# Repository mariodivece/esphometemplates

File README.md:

# My ESPHome Templates

(Work in progress)

device classes:
 - [Analog Device Classes](https://www.home-assistant.io/integrations/sensor/#device-class)
 - [Binary Device Classes](https://www.home-assistant.io/integrations/binary_sensor/#device-class)
 - [NodeMCU 32s Pinout](https://www.waveshare.com/nodemcu-32s.htm)

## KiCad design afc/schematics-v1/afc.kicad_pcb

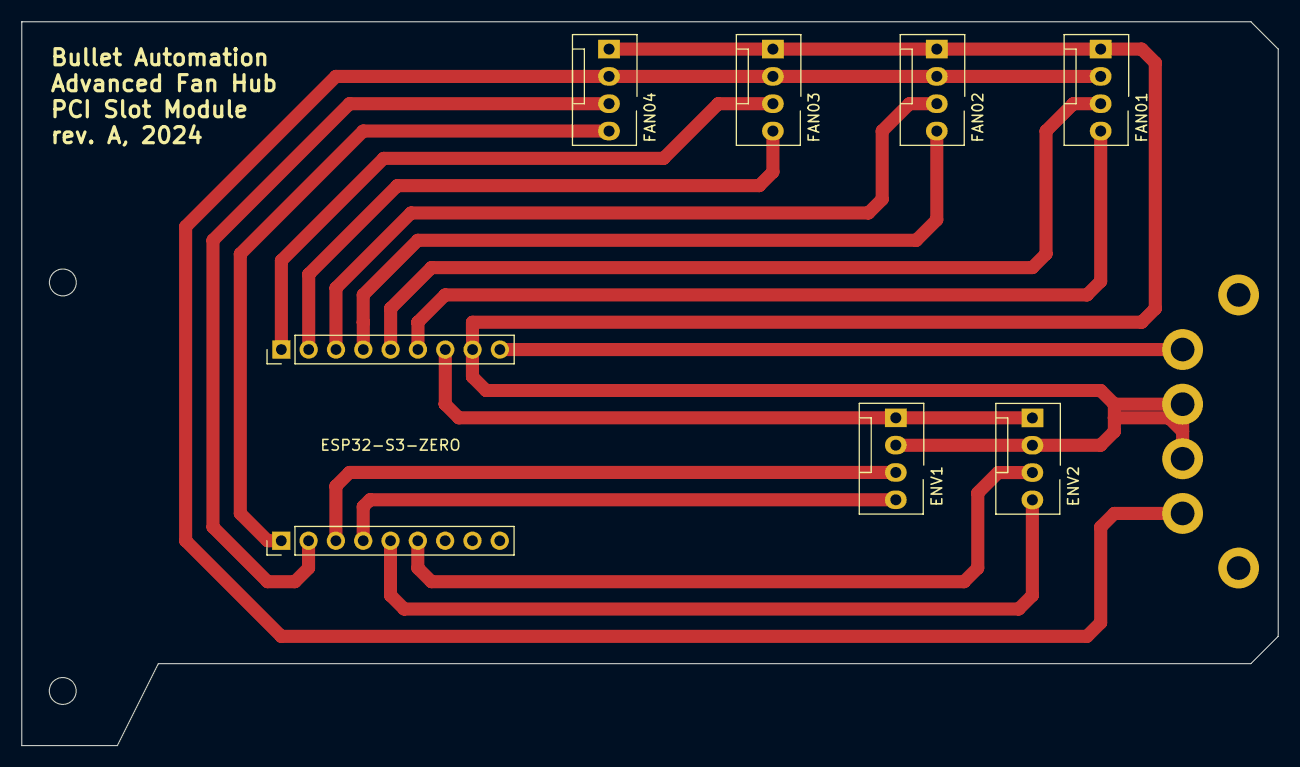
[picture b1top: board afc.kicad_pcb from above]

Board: 2 copper layers, 116.8 x 67.3 mm, 11 parts (0 on the bottom side), 15 nets.

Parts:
ATX2, ATX3: MountingHole_2.2mm_M2_DIN965_Pad
ENV1, ENV2: FAN_H4; FanPinHeader_1x04_P2.54mm_Vertical
ESP32_A: HA; PinHeader_1x09_P2.54mm_Vertical
ESP32_B: HB; PinHeader_1x09_P2.54mm_Vertical
FAN01: FAN_H1; FanPinHeader_1x04_P2.54mm_Vertical
FAN02: FAN_H2; FanPinHeader_1x04_P2.54mm_Vertical
FAN03: FAN_H3; FanPinHeader_1x04_P2.54mm_Vertical
FAN04: FAN_H4; FanPinHeader_1x04_P2.54mm_Vertical
PCIe_MNT_TOP: MountingHole_2.5mm

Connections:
3V3: ENV1.1, ENV2.1, ESP32_A.3V3
12V: FAN01.2, FAN02.2, FAN03.2, FAN04.2
GND: ATX2.2, ATX3.3, ENV1.2, ENV2.2, ESP32_A.GND, FAN01.1, FAN02.1, FAN03.1, FAN04.1
PWM1: ESP32_A.1, FAN01.4
PWM2: ESP32_A.3, FAN02.4
PWM3: ESP32_A.5, FAN03.4
PWM4: ESP32_B.7, FAN04.4
SCL_1: ENV1.3, ESP32_B.9
SCL_2: ENV2.3, ESP32_B.12
SDA_1: ENV1.4, ESP32_B.10
SDA_2: ENV2.4, ESP32_B.11
TACHO1: ESP32_A.2, FAN01.3
TACHO2: ESP32_A.4, FAN02.3
TACHO3: ESP32_A.6, FAN03.3
TACHO4: ESP32_B.8, FAN04.3

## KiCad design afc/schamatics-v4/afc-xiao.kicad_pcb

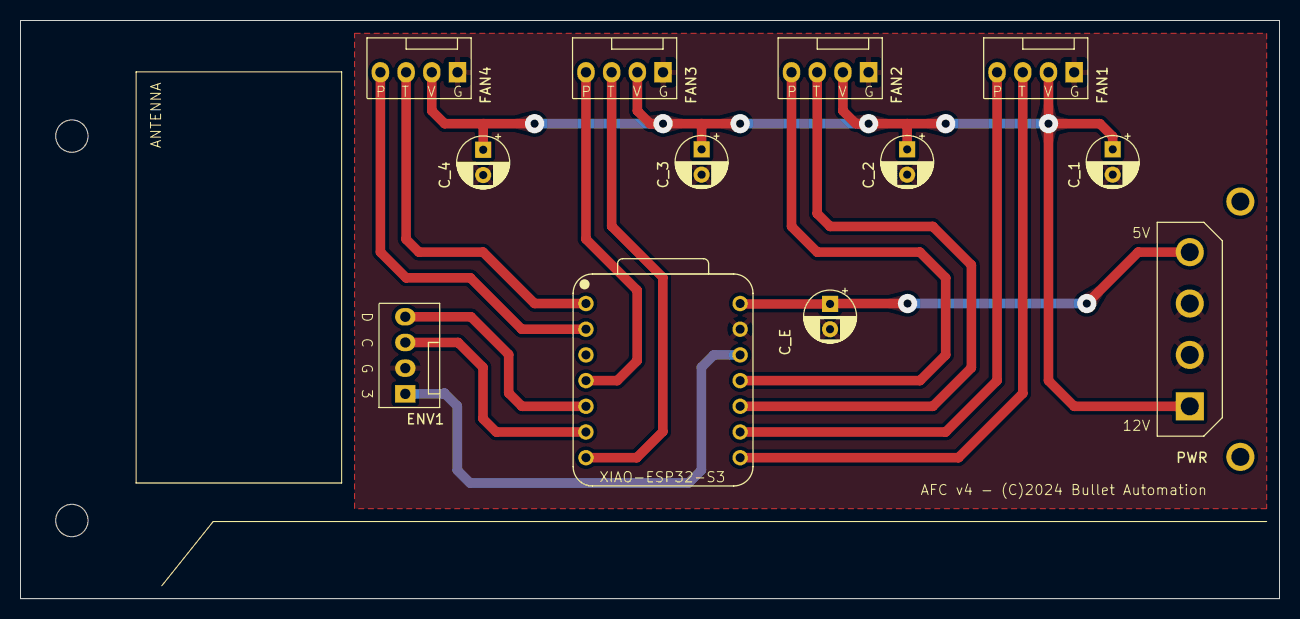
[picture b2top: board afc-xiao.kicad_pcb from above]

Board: 2 copper layers, 124.5 x 57.1 mm, 12 parts (0 on the bottom side), 14 nets.

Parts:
C_1, C_2, C_3, C_4: CP_Radial_D5.0mm_P2.50mm
C_E: CP_Radial_D5.0mm_P2.50mm
ENV1: PWM 4-pin Fan Header
FAN1, FAN2, FAN3, FAN4: PWM 4-pin Fan Header
PWR: Molex 4-Pin Power Connector
XIAO-ESP32-S3: XIAO-ESP32-S3-DIP; XIAO-ESP32S3-DIP

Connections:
3V3: ENV1.1, XIAO-ESP32-S3.12
5V: C_E.1, PWR.4, XIAO-ESP32-S3.14
12V: C_1.1, C_2.1, C_3.1, C_4.1, FAN1.2, FAN2.2, FAN3.2, FAN4.2, PWR.1
GND: C_1.2, C_2.2, C_3.2, C_4.2, C_E.2, ENV1.2, FAN1.1, FAN2.1, FAN3.1, FAN4.1, PWR.2, PWR.3, XIAO-ESP32-S3.13
PWM1: FAN1.4, XIAO-ESP32-S3.9
PWM2: FAN2.4, XIAO-ESP32-S3.11
PWM3: FAN3.4, XIAO-ESP32-S3.4
PWM4: FAN4.4, XIAO-ESP32-S3.2
SCL: ENV1.3, XIAO-ESP32-S3.6
SDA: ENV1.4, XIAO-ESP32-S3.5
TACHO1: FAN1.3, XIAO-ESP32-S3.8
TACHO2: FAN2.3, XIAO-ESP32-S3.10
TACHO3: FAN3.3, XIAO-ESP32-S3.7
TACHO4: FAN4.3, XIAO-ESP32-S3.1

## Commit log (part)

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2024-02-10 repo update
2024-02-10 removing subs
2024-02-10 remove subs
2024-02-10 fix typo
2024-02-10 updating 2g
2024-02-10 fixing hostname
2024-02-10 better name
2024-02-10 updating import definitions
2024-02-10 minor fix
2024-02-10 lab update
2024-02-10 simplifying substitutions
2024-02-10 minor doc
2024-02-10 simplifying 1g and 2g
2024-02-10 moving samples to folder
2024-02-10 adding d1 dimmer
2024-02-10 substitutions
2024-02-10 separating internaltemp
2024-02-10 trying out number configs
2024-02-10 scrubbing
2024-02-10 updating README
2024-02-12 Update sonoff-d1.yaml
    attempting to make the min and max levels UI-configurable
2024-02-12 upgrading sonoff d1
2024-02-12 fixing script
2024-02-12 testing
2024-02-13 attempting state synchronization
2024-02-13 minor fixup
2024-02-13 removing state accessor
2024-02-13 controller hanging
2024-02-13 toggle to sync
2024-02-13 minor id fix
2024-02-13 removing togglers
2024-02-13 removing unusable options
2024-02-13 gamma correct
2024-02-13 momentary support
2024-02-13 upgrading and adjusting modes
2024-02-14 adding initial version of shelly dimmer 2
2024-02-14 using correct name of dimmer device
2024-02-14 minor doc fix
2024-02-14 simplifying shelly dimmer2 firmware template
2024-02-14 splitting up shelly dimmer
2024-02-15 renaming and pointing to new package locations
2024-02-15 device model
2024-02-15 starting with rgbw2
2024-02-15 removing update_interval
2024-02-15 trying to fix scripts
2024-02-15 adding board
2024-02-15 separating input switch
2024-02-15 strapping warning
2024-02-15 fixing reference
2024-02-15 script
2024-02-15 pointers
2024-02-15 color values
2024-02-15 minor comments
2024-02-15 minor formatting
2024-02-16 major refactoring and improvements. Yet to be tested out
2024-02-16 removing usemac
2024-02-16 renaming timing_momentary to timing_pulse
2024-02-16 light synchronization
2024-02-16 attempting fix
2024-02-16 array init
2024-02-16 make_Call
2024-02-16 removing substitution
2024-02-16 testing substitution removal
2024-02-16 removing substitutions
2024-02-16 removing substitutions for sonoff-m5
2024-02-16 ordering subs
2024-02-16 attempting to move substitution includes
2024-02-16 substitutions and defaults
2024-02-16 removing more subs
2024-02-16 adding shelly rgbw2 virtual buttons
2024-02-16 bad sync
2024-02-16 minor bugfix
2024-02-16 minor changes
2024-02-16 minor indent
2024-02-16 ploynomial
2024-02-17 uptime sensors
2024-02-17 uptime fix
2024-02-17 updating c++ string
2024-02-17 sensor
2024-02-17 calibration
2024-02-17 light sync
2024-02-17 scripting
2024-02-17 more scripting
2024-02-17 cleaning up
2024-02-17 minor chang in virtual buttons
2024-02-21 adding TODO for power saving
2024-02-27 improving standard libraries
2024-02-27 trying to aplit up radar configuration
2024-02-27 zoning config
2024-02-27 continued work on radar
2024-02-27 simplifying
2024-02-27 occupancy simplified
2024-02-27 indent
2024-02-27 renaming certain entities
2024-02-27 minor typo
2024-02-29 adding S3 version
2024-04-27 bullet s3
2024-04-27 continues s3
2024-04-27 changing ports for radar
2024-04-27 still testing radar
2024-04-27 radar under peripherals
2024-04-28 testing out audio
2024-04-28 adding bus id and substitutions
2024-04-28 testing out stereo output
2024-04-28 onboard LED first test
2024-04-28 adding illuminance over i2c
2024-04-28 adding bme680 to bullet s3
2024-04-28 removing bme
2024-04-28 fix in bme680
2024-04-28 adding pwm lighting
2024-04-29 adding microphone
2024-04-29 attempting sound level meter
2024-04-29 test sound level meter
2024-04-29 naming
2024-04-29 reference
2024-04-29 trying to get microphone to work
2024-05-01 trying to get mic to work
2024-05-01 offset
2024-05-01 another attempt at sound
2024-05-01 left channel test
2024-05-01 attempting to remove neopixel bus
2024-05-01 missing id
2024-05-01 attempting to remove arduino
2024-05-01 back to arduino (music player)
2024-05-01 back to latest
2024-05-01 trying a different channel?
2024-05-01 adding bus id
2024-05-01 fixing pin mappings for microphone
2024-05-01 removing apll and changing to left channel
2024-05-01 back to right channel
2024-05-01 back to regular microphone
2024-05-01 adding channel to microphone
2024-05-01 first attempt at voice assistant
2024-05-01 minor id fixes
2024-05-01 audio out
2024-05-01 no name for speaker
2024-05-01 audio bus id
2024-05-01 trying to get assist to work
2024-05-01 minor change in ids
2024-05-01 changing channel
2024-05-01 testing left
2024-11-24 adding advanced fan controller
2024-11-24 renaming
2024-11-24 ota fixing
2024-11-24 latest version
2024-11-24 removing safe_mode config from OTA and towards its own config
2024-11-24 lowering i2c speed
2024-11-24 adding icons
2024-11-24 initial substitutions
2024-11-24 light effects
2024-11-24 effects and reboot disable
2024-11-24 update test
2024-11-24 typo fix
2024-11-25 pulse
2024-11-25 status pulse
2024-11-25 initial color?
2024-11-25 on tun on
2024-11-25 initial state
2024-11-25 color transitions
2024-11-25 indentation
2024-11-25 Pulsing
2024-11-25 prevent exposure of Status LED
2024-11-25 id substitution testing
2024-11-25 more substitutions
2024-11-25 string sub
2024-11-25 minor refactoring
2024-11-25 typos
2024-11-25 minimum fan power
2024-11-28 webserver improvements
2024-11-30 adding v2 fan hub
2024-11-30 refactoring, adding fan label, more substitutions
2024-11-30 adding ambient sensor label
2024-11-30 adding rssi icon
2024-11-30 adding missing icons
2024-12-02 adding kicad schematics and PCB
2024-12-02 updating kicad schematics
2024-12-03 trying out labdas
2024-12-03 typo
2024-12-03 pointers.,,,
2024-12-03 structs...
2024-12-03 automatic fan 1 control
2024-12-03 temperature parameters
2024-12-04 adding basic
2024-12-04 removing internal temp
2024-12-05 adding v2 schematics
2024-12-05 improvements on PCB design
2024-12-05 more cleanup
2024-12-06 moving controller on to a different file.
2024-12-07 ground plane for schematic
2024-12-08 updating schematic
2024-12-08 fan parameters change
2024-12-12 temp disable auto speed
2024-12-12 min fan speed
2024-12-12 automatic parameters set
2024-12-12 better parameters
2024-12-13 adding v3 PCB
2024-12-15 adding xiao s3
2024-12-15 monochromatic light
2024-12-15 updating board
2024-12-15 changing pwm channel
2024-12-15 updating PCB
2024-12-15 adding pcbway design!
2024-12-27 minor update to gitignore
2024-12-27 afc v4
2024-12-27 removing controller
2024-12-28 afcv2 minimal changes
2024-12-28 afcv4 subs
2025-04-13 petlive v1
2025-04-13 updating
2025-04-18 vastly improving petlitev1
2025-04-18 minor change
2025-04-18 webserver
2025-04-18 GPIO mappings
2025-04-18 output template
2025-04-18 trying number as output
2025-04-18 colors
2025-04-18 external button
2025-04-18 bme setup
2025-04-18 ghello
2025-04-18 values
2025-04-18 globals maybe?
2025-04-18 globals
2025-04-18 lambda
2025-04-18 i2c bus id
2025-04-18 i2c id
2025-04-18 i2c address
2025-04-18 gloablas and UI
2025-04-18 Battery meter
2025-04-18 decimals accuracy
2025-04-19 fixing power supply
2025-04-19 remove internal temp
2025-04-19 attempt reset
2025-04-19 i2c priority
2025-04-19 power on
2025-04-19 boot
2025-04-19 high priority on
2025-04-19 reset code
2025-04-19 minor UI changes
2025-04-19 various improvements
2025-04-19 icons
2025-04-19 minor UI fixes
2025-04-19 internal light
2025-04-19 starting with time automation
2025-04-19 if then
2025-04-19 info
2025-04-19 script calling
2025-04-19 sync start
2025-04-19 demo sleep!
2025-04-19 trigger
2025-04-19 restart
2025-04-19 committ
2025-04-19 demo
2025-04-19 no return
2025-04-19 nodelay
2025-04-19 no while
2025-04-19 no while?
2025-04-19 no delay
2025-04-20 lightcolorvalues global
2025-04-20 attempt change detection
2025-04-20 color values?
2025-04-20 pointers?
2025-04-20 names?
2025-04-20 names
2025-04-20 debug
2025-04-20 sleep
2025-04-20 removing globals
2025-04-20 no code at all?
2025-04-20 getting light states?
2025-04-20 remote values
2025-04-20 logging
2025-04-20 remove logging
2025-04-20 getting red
2025-04-20 log red
2025-04-20 no args
2025-04-20 minimal logging
2025-04-20 logging red
2025-04-20 autos
2025-04-20 light names
2025-04-20 valueS?
2025-04-20 more logging
2025-04-20 globals?
2025-04-20 full qualifiers
2025-04-20 static
2025-04-20 logging last
2025-04-20 change detection
2025-04-20 checking
2025-04-20 dereference comparison
2025-04-20 copy
2025-04-20 lambdas?
2025-04-20 lambdas
2025-04-20 apply?
2025-04-20 logging?
2025-04-20 time loop, better logging
2025-04-20 time arithmetic
2025-04-20 using interval component
2025-04-20 more arithmetic
2025-04-20 minutes
2025-04-20 arithmetic
2025-04-21 schedule
2025-04-21 captures
2025-04-21 variable names
2025-04-21 case handle
2025-04-21 publish
2025-04-21 String concatenation
2025-04-21 concat?
2025-04-21 light apply
2025-04-21 wake light demo
2025-04-21 changing info to DEBUG
2025-04-21 bumpiing up version
2025-04-21 adding TODOS
2025-04-24 battery calibation, leave light output alone if not changed.
2025-04-24 attenuation of 11db
2025-04-24 no off alternation
2025-04-24 battery calibration
2025-04-24 automatic attenuation
2025-04-24 using board name
2025-04-24 restore board
2025-04-24 text sensor
2025-04-24 string return
2025-04-24 typo?
2025-04-24 internal maybe?
2025-04-24 sensor template
2025-04-24 minor typos
2025-04-24 diagnostic
2025-04-24 text-sensor
2025-04-27 led variant and led count
2025-04-27 variants
2025-09-06 Change WiFi power save mode to 'light'
2025-09-06 Add ap_timeout setting to wifi.yaml
2025-12-27 fixing ntp time
2026-01-03 reducing reporting frequency for petlites
2026-01-03 reverting settings for sensor

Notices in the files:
afc/schamatics-v4/afc-xiao.kicad_pcb:
AFC v4 - (C)2024 Bullet Automation
